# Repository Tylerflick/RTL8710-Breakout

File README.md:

# RTL8710-Breakout
Breakout board and component libraries for RTL8710 (RTL01) module.

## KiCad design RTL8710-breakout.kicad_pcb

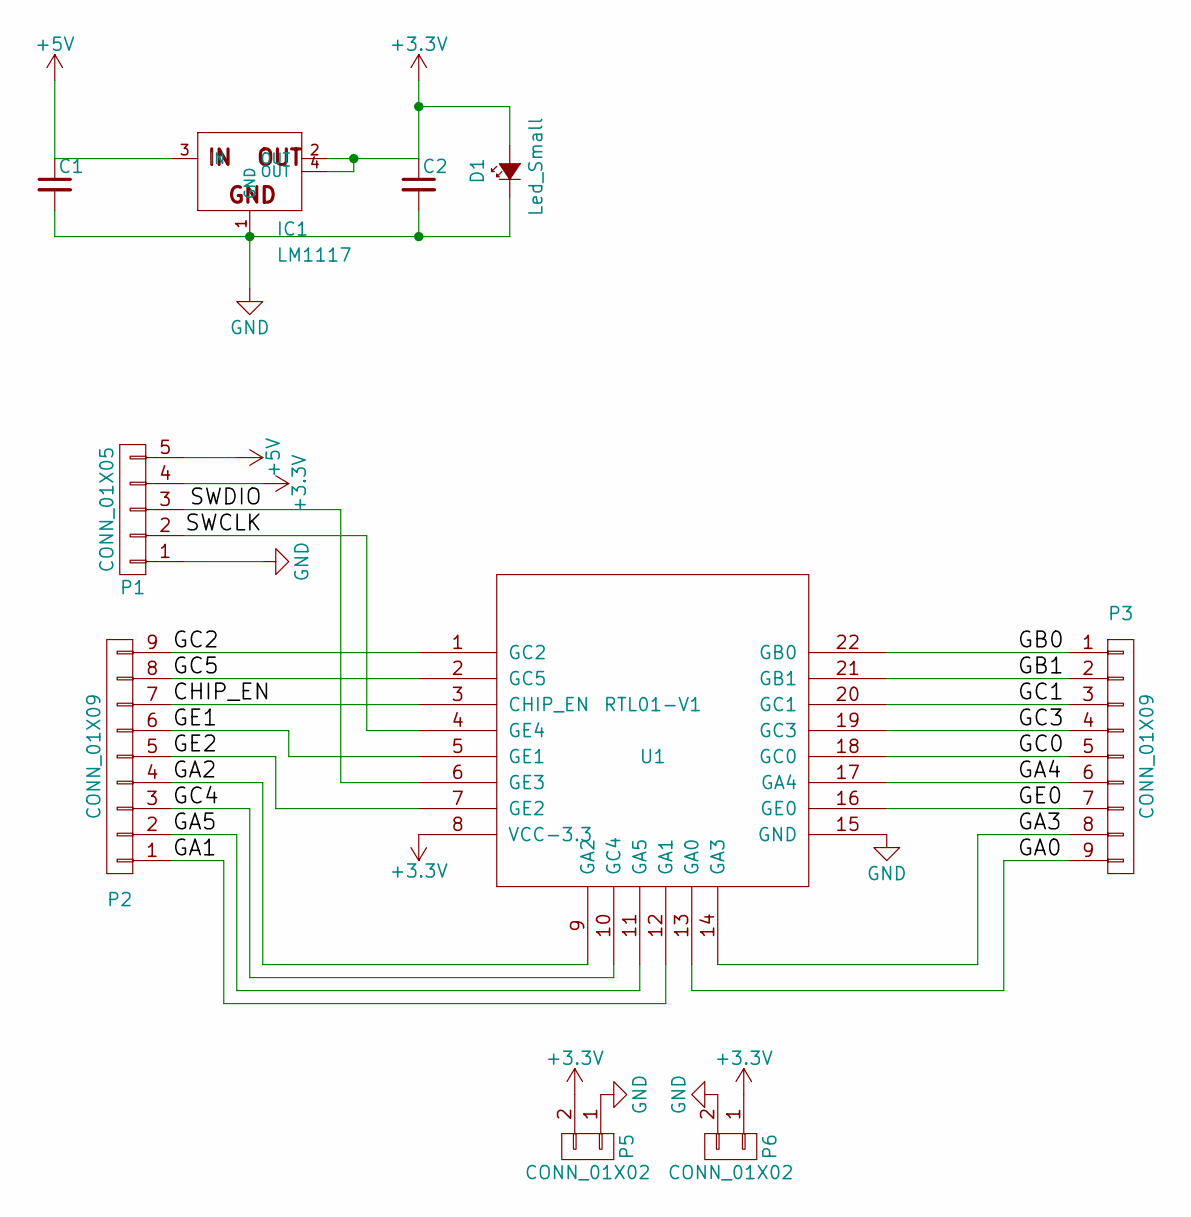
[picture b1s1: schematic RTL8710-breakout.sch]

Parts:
C1, C2: 10uf; C_0805_HandSoldering
D1: Led_Small; LED_0603
IC1: LM1117; SOT-223
P1: CONN_01X05; CONN_2.54mm_1x5
P2, P3: CONN_01X09; CONN_2.54mm_1x9
P5, P6: CONN_01X02; CONN_2.54mm_1x2
U1: RTL01-V1

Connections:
+3V3: C2.1, D1.2 (A), IC1.2 (OUT), IC1.4 (OUT), P1.4, P5.2, P6.1, U1.8 (VCC-3.3)
+5V: C1.1, IC1.3 (IN), P1.5
/CHIP_EN: P2.7, U1.3 (CHIP_EN)
/GA0: P3.9, U1.13 (GA0)
/GA1: P2.1, U1.12 (GA1)
/GA2: P2.4, U1.9 (GA2)
/GA3: P3.8, U1.14 (GA3)
/GA4: P3.6, U1.17 (GA4)
/GA5: P2.2, U1.11 (GA5)
/GB0: P3.1, U1.22 (GB0)
/GB1: P3.2, U1.21 (GB1)
/GC0: P3.5, U1.18 (GC0)
/GC1: P3.3, U1.20 (GC1)
/GC2: P2.9, U1.1 (GC2)
/GC3: P3.4, U1.19 (GC3)
/GC4: P2.3, U1.10 (GC4)
/GC5: P2.8, U1.2 (GC5)
/GE0: P3.7, U1.16 (GE0)
/GE1: P2.6, U1.5 (GE1)
/GE2: P2.5, U1.7 (GE2)
/SWCLK: P1.2, U1.4 (GE4)
/SWDIO: P1.3, U1.6 (GE3)
GND: C1.2, C2.2, D1.1 (K), IC1.1 (GND), P1.1, P5.1, P6.2, U1.15 (GND)

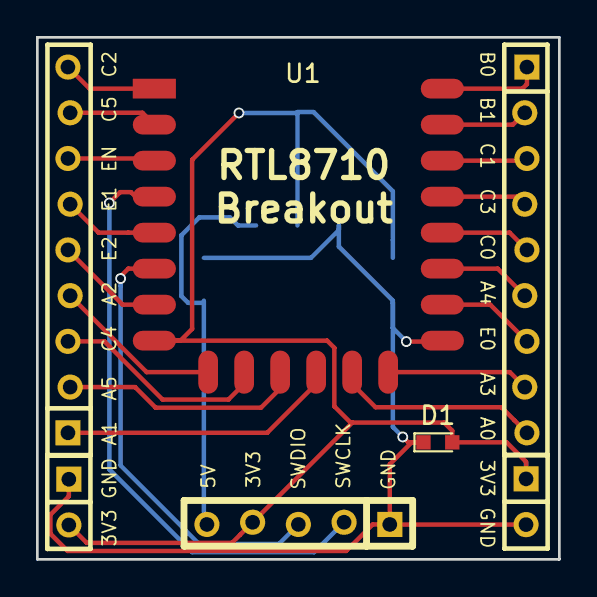
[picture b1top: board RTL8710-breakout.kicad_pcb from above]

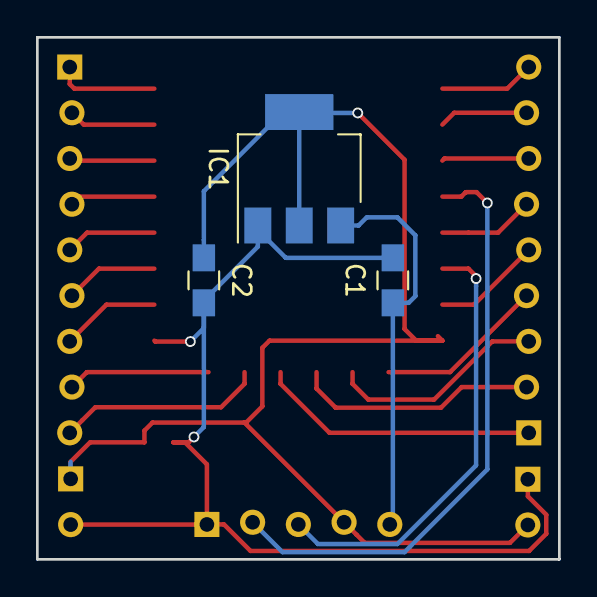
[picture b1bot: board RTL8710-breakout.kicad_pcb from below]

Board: 2 copper layers, 29.0 x 29.0 mm, 10 parts (3 on the bottom side), 23 nets.

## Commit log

2017-01-24 Add IC image
2017-01-24 Add README
2017-01-29 add SWD interface
2017-01-31 add connections to breakout schematic
2017-01-31 finsh pcb layout
